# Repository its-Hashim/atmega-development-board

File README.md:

# atmega-development-board

I have created this atmega development board for a line following robot for a client.
This line following robot is a trolley which follows line and stop at its station.
The repository contains only the design atmega development board just to give some idea how this board is designed.
Everyone has full right to clone this design and manufacture development board directly from this design.
The development board can be used for other porpose such as for learning porpose.

Feel free to give any suggestion and ask question.
Thank you.

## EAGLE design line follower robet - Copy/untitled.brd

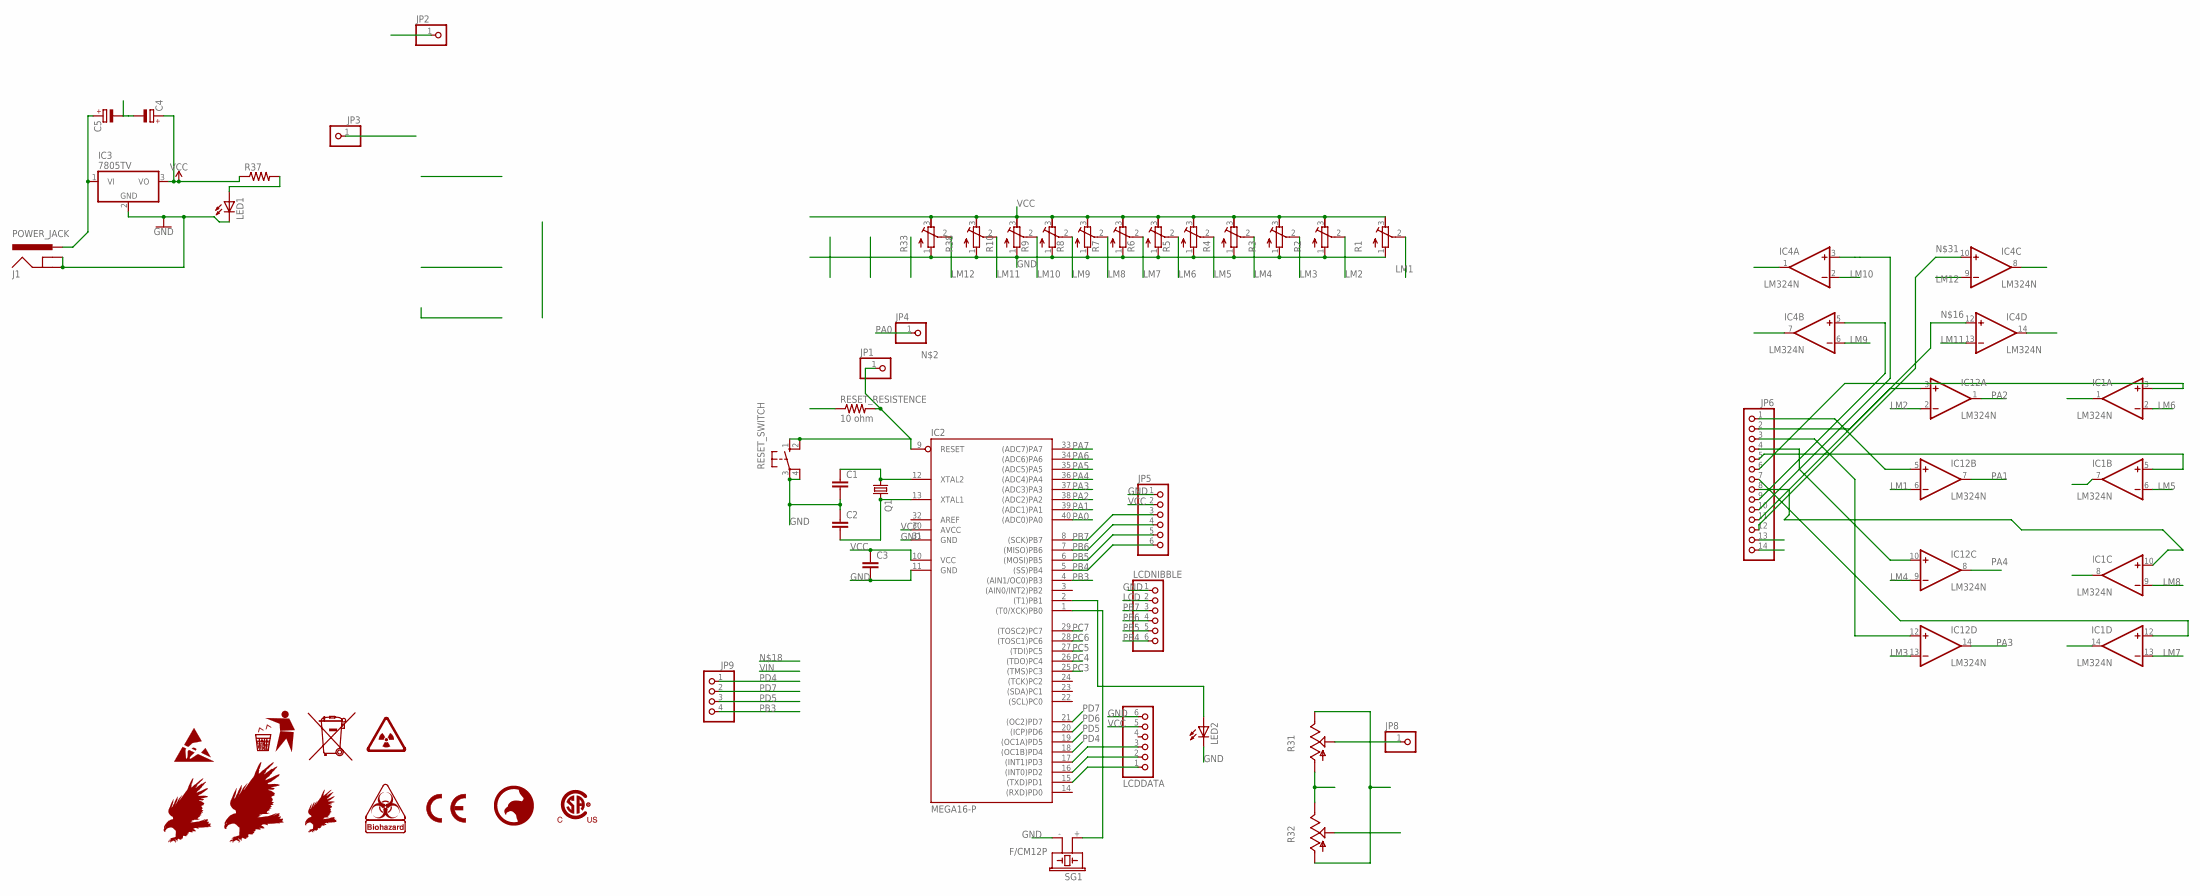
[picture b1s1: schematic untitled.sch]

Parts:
C1, C2: C-EU025-025X050; C025-025X050
C3: C-EU050-030X075; C050-030X075
C4, C5: CPOL-EUE2.5-6; E2,5-6
IC1, IC4, IC12: LM324N; DIL14
IC2: MEGA16-P; DIL40
IC3: 7805TV; TO220V
J1: POWER_JACK; POWER_JACK_PTH
JP1, JP2, JP3, JP4, JP8: PINHD-1X1; 1X01
JP5: PINHD-1X6; 1X06
JP6: PINHD-1X14/90; 1X14/90
JP9: PINHD-1X4; 1X04
LCDDATA: PINHD-1X6; 1X06
LCDNIBBLE: PINHD-1X6; 1X06
LED1, LED2: LED5MM
Q1: CRYSTALHC49U70; HC49U70
R1, R2, R3, R4, R5, R6, R7, R8, R9, R10, R33, R38: R-TRIMM64W; RTRIM64W
R31, R32: TRIM_US-CA9V; CA9V
R37: R-US_0204/7; 0204/7
RESET_RESISTENCE: 10 ohm; 0204/7
RESET_SWITCH: 10-XX; B3F-10XX
SG1: F/CM12P

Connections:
GND: C1.2, C2.1, C3.2, C4.-, C5.-, IC2.11 (GND), IC2.31 (GND), IC3.2 (GND), J1.GND, J1.GNDBREAK, JP2.1, JP5.1, JP6.14, LCDDATA.6, LCDNIBBLE.1, LED1.K (C), LED2.K (C), R1.1 (A), R2.1 (A), R3.1 (A), R4.1 (A), R5.1 (A), R6.1 (A), R7.1 (A), R8.1 (A), R9.1 (A), R10.1 (A), R31.A, R32.E, R33.1 (A), R38.1 (A), RESET_SWITCH.3, RESET_SWITCH.4 (P1), SG1.- (2)
LCD: LCDNIBBLE.2, R32.S
LM1: IC12.6 (-IN), R1.2 (S)
LM2: IC12.2 (-IN), R2.2 (S)
LM3: IC12.13 (-IN), R3.2 (S)
LM4: IC12.9 (-IN), R4.2 (S)
LM5: IC1.6 (-IN), R5.2 (S)
LM6: IC1.2 (-IN), R6.2 (S)
LM7: IC1.13 (-IN), R7.2 (S)
LM8: IC1.9 (-IN), R8.2 (S)
LM9: IC4.6 (-IN), R9.2 (S)
LM10: IC4.2 (-IN), R10.2 (S)
LM11: IC4.13 (-IN), R38.2 (S)
LM12: IC4.9 (-IN), R33.2 (S)
unnamed: IC2.9 (RESET), JP1.1, RESET_RESISTENCE.2, RESET_SWITCH.1 (S), RESET_SWITCH.2 (S1)
unnamed: IC1.10 (+IN), JP6.8
unnamed: C1.1, IC2.12 (XTAL2), Q1.1
unnamed: C2.2, IC2.13 (XTAL1), Q1.2
unnamed: IC2.15 ((TXD)PD1), LCDDATA.1
unnamed: IC2.16 ((INT0)PD2), LCDDATA.2
unnamed: IC2.17 ((INT1)PD3), LCDDATA.3
unnamed: IC12.12 (+IN), JP6.3
unnamed: IC12.10 (+IN), JP6.4
unnamed: IC12.5 (+IN), JP6.1
unnamed: IC12.3 (+IN), JP6.2
unnamed: IC4.12 (+IN), JP6.11
unnamed: C5.+, IC3.1 (VI), J1.PWR
unnamed: JP8.1, R31.S
unnamed: LED1.A, R37.2
unnamed: IC2.1 ((T0/XCK)PB0), SG1.+ (1)
unnamed: IC2.2 ((T1)PB1), LED2.A
unnamed: IC4.10 (+IN), JP6.12
unnamed: IC1.3 (+IN), JP6.6
unnamed: IC1.5 (+IN), JP6.5
unnamed: IC1.12 (+IN), JP6.7
unnamed: IC4.3 (+IN), JP6.10
unnamed: IC4.5 (+IN), JP6.9
PA0: IC2.40 ((ADC0)PA0), JP4.1
PA1: IC2.39 ((ADC1)PA1), IC12.7 (OUT)
PA2: IC2.38 ((ADC2)PA2), IC12.1 (OUT)
PA3: IC2.37 ((ADC3)PA3), IC12.14 (OUT)
PA4: IC2.36 ((ADC4)PA4), IC12.8 (OUT)
PA5: IC1.7 (OUT), IC2.35 ((ADC5)PA5)
PA6: IC1.1 (OUT), IC2.34 ((ADC6)PA6)
PA7: IC1.14 (OUT), IC2.33 ((ADC7)PA7)
PB3: IC2.4 ((AIN1/OC0)PB3), JP9.4
PB4: IC2.5 ((SS)PB4), JP5.6, LCDNIBBLE.6
PB5: IC2.6 ((MOSI)PB5), JP5.5, LCDNIBBLE.5
PB6: IC2.7 ((MISO)PB6), JP5.4, LCDNIBBLE.4
PB7: IC2.8 ((SCK)PB7), JP5.3, LCDNIBBLE.3
PC3: IC2.25 ((TMS)PC3), IC4.8 (OUT)
PC4: IC2.26 ((TDO)PC4), IC4.14 (OUT)
PC5: IC2.27 ((TDI)PC5), IC4.1 (OUT)
PC6: IC2.28 ((TOSC1)PC6), IC4.7 (OUT)
PC7: IC1.8 (OUT), IC2.29 ((TOSC2)PC7)
PD4: IC2.18 ((OC1B)PD4), JP9.1
PD5: IC2.19 ((OC1A)PD5), JP9.3
PD6: IC2.20 ((ICP)PD6)
PD7: IC2.21 ((OC2)PD7), JP9.2
V+: IC1.4 (V+), IC4.4 (V+), IC12.4 (V+)
V-: IC1.11 (V-), IC4.11 (V-), IC12.11 (V-)
VCC: C3.1, C4.+, IC2.10 (VCC), IC2.30 (AVCC), IC3.3 (VO), JP3.1, JP5.2, JP6.13, LCDDATA.5, R1.3 (E), R2.3 (E), R3.3 (E), R4.3 (E), R5.3 (E), R6.3 (E), R7.3 (E), R8.3 (E), R9.3 (E), R10.3 (E), R31.E, R32.A, R33.3 (E), R37.1, R38.3 (E), RESET_RESISTENCE.1

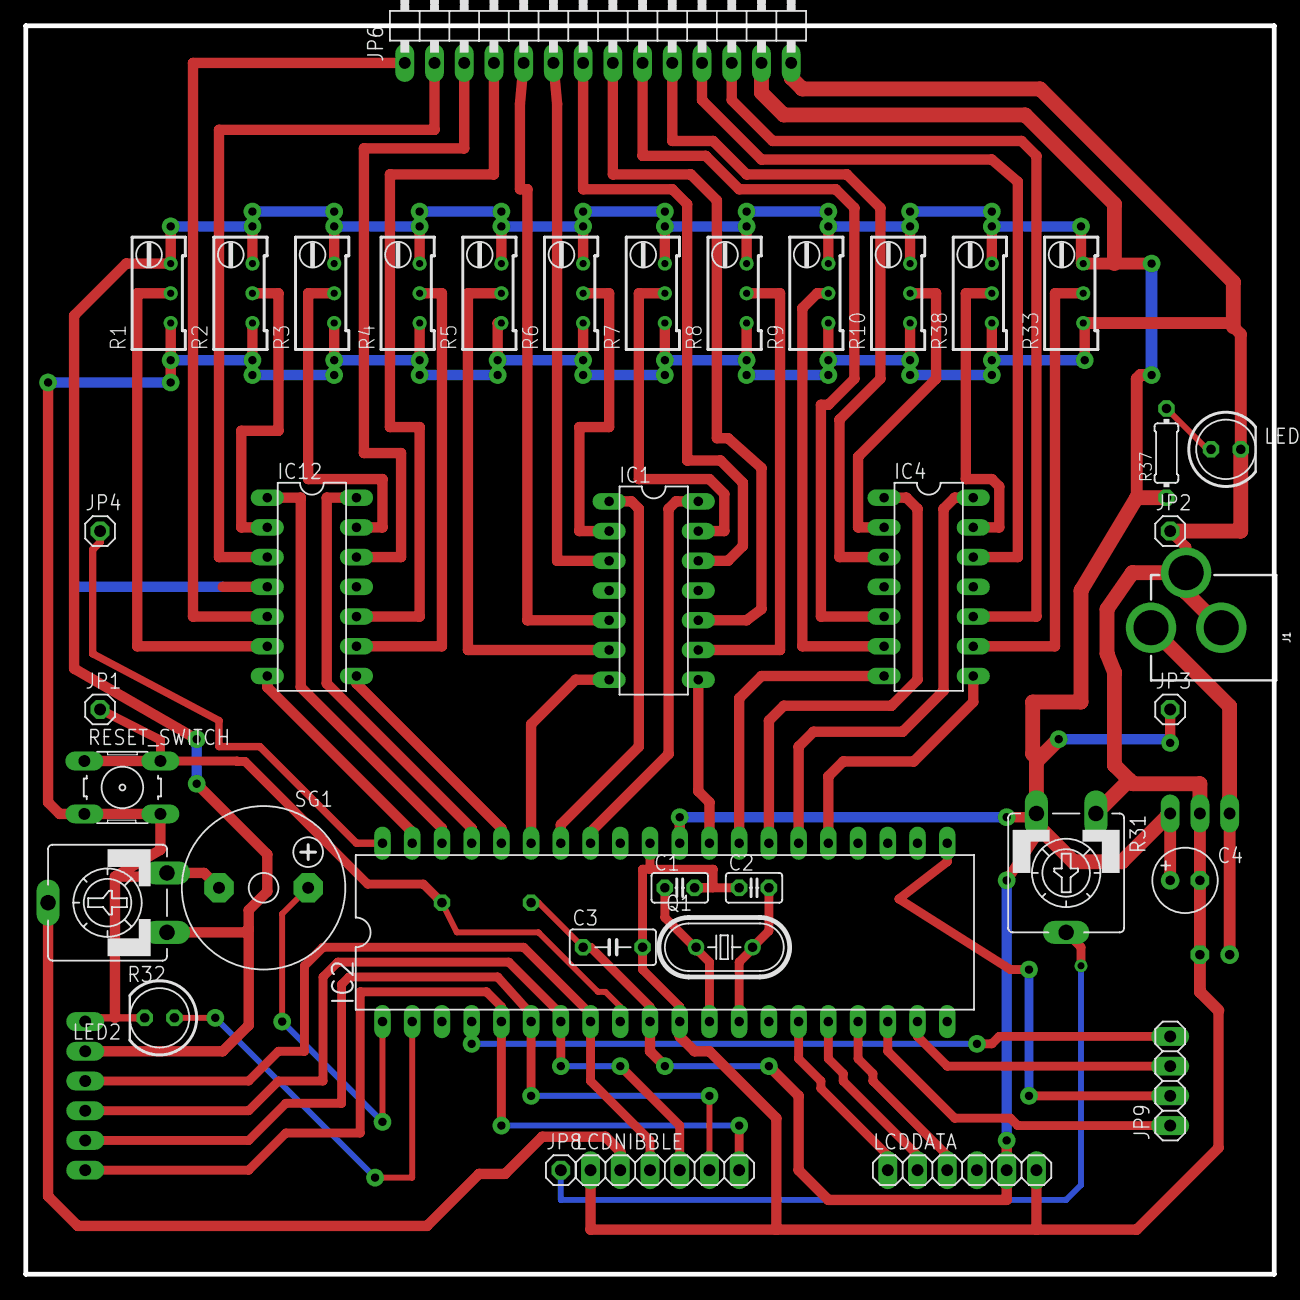
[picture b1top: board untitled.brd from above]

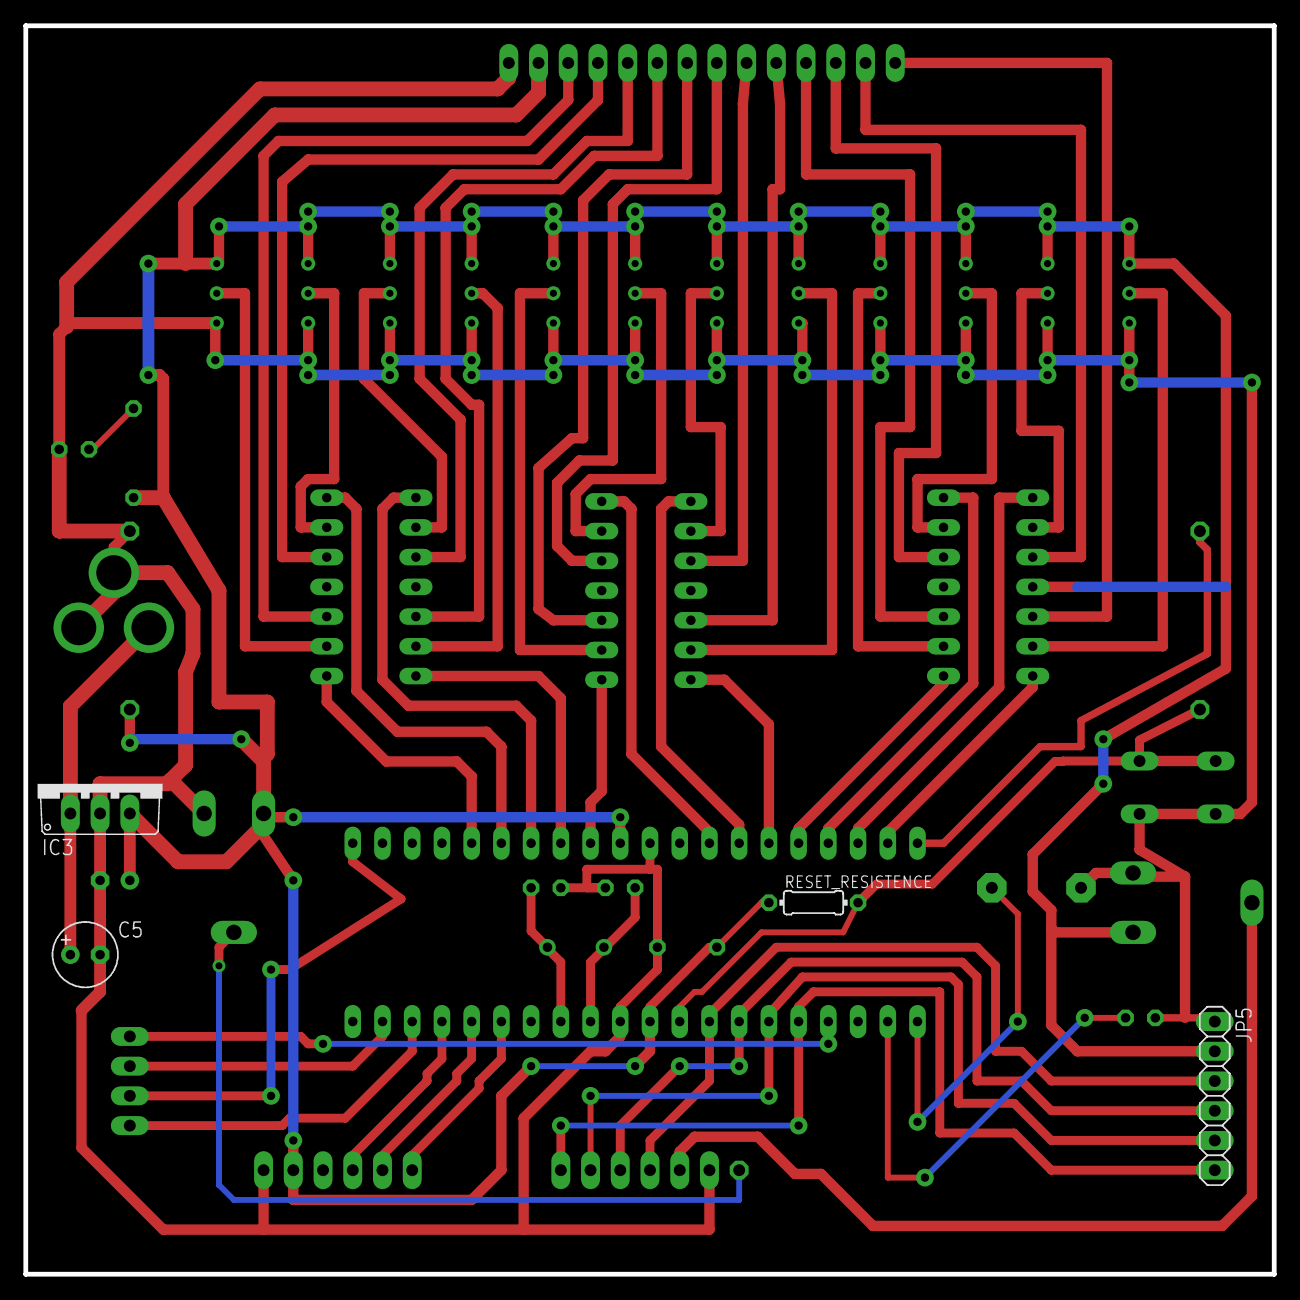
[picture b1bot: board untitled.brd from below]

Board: 2 copper layers, 106.7 x 106.7 mm, 42 parts (4 on the bottom side), 61 nets.

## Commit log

2017-10-03 file added

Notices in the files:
parts and their libraries:
SparkFun-Connectors: Licensing: Creative Commons ShareAlike 4.0 International - https://creativecommons.org/licenses/by-sa/4.0
